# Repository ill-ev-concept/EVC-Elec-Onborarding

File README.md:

@ -1,42 +0,0 @@
# EVC-Elec-Onborarding

Hello onboarding members!

We're going to use this repo as a way for you guys to get practice using Github and EV Concepts workflow. This repo is going to be organized the same way that our main repo (EVC-PCB) is. 

First, let us look at what you need before you start. You need to download at least KiCAD 10 and Git. I also recommened getting Github Desktop

https://www.kicad.org/download/\
https://git-scm.com/install/\
https://desktop.github.com/download/

Also take a look at the documentation for our main repo. We will follow the exact same structure, but change a few variables in order for it to function with this repo. 

https://github.com/ill-ev-concept/EVC-PCB/blob/main/README.md

Let's look at the section where we set paths in KiCAD. We use ```EVC_SYMBOL_DIR```, ```EVC_FOOTPRINT_DIR```, and ```EVC_3DMODEL_DIR``` as variables to set paths for our main repo. In this repo, we will be using different paths. Create three varibles called ```EVCOB_SYMBOL_DIR```, ```EVCOB_FOOTPRINT_DIR```, and ```EVCOB_3DMODEL_DIR```. Link these to the location of the ```symbols```, ```footprints```, and ```3d_models``` folders contained with ```libs-ob``` folder.

It should look like below:

Similarly, we will be needing KiCAD to look at the given library. We can do this by going to "Preferences" and finding either "Manage Symbol Libraries" or "Manage Footprint Libraries". Opening either brings up a window where we can select "Project Specific Libraries" where we can add paths. Click the folder icon and add the wanted library. If you set the path up correctly, the library path will contain  ```${EVCON_SYMBOL_DIR}```, ```${EVCON_FOOTPRINT_DIR}```, or ```${EVCON_3DMODEL_DIR}```. 

It will look like below if done correctly.

Now that your paths are set up properly, its important to use Git and Github properly. Read the Contributing section of EVC-PCB's README file. It goes into detail of how to contribute and properly pull, merge, and create PRs.

Make sure to push and pull from this specific repo, EVC-Elec-Onboarding, not EVC-PCB. EVC-PCB will be the repo you work in after onboarding. Right now, we want to see your work in this repo.

If you have any questions, feel free to message either Miles (mileskubik), Himesh (hotmesh), or Ethan (whybd) on Discord or find us after a meeting. 

Good luck designing!

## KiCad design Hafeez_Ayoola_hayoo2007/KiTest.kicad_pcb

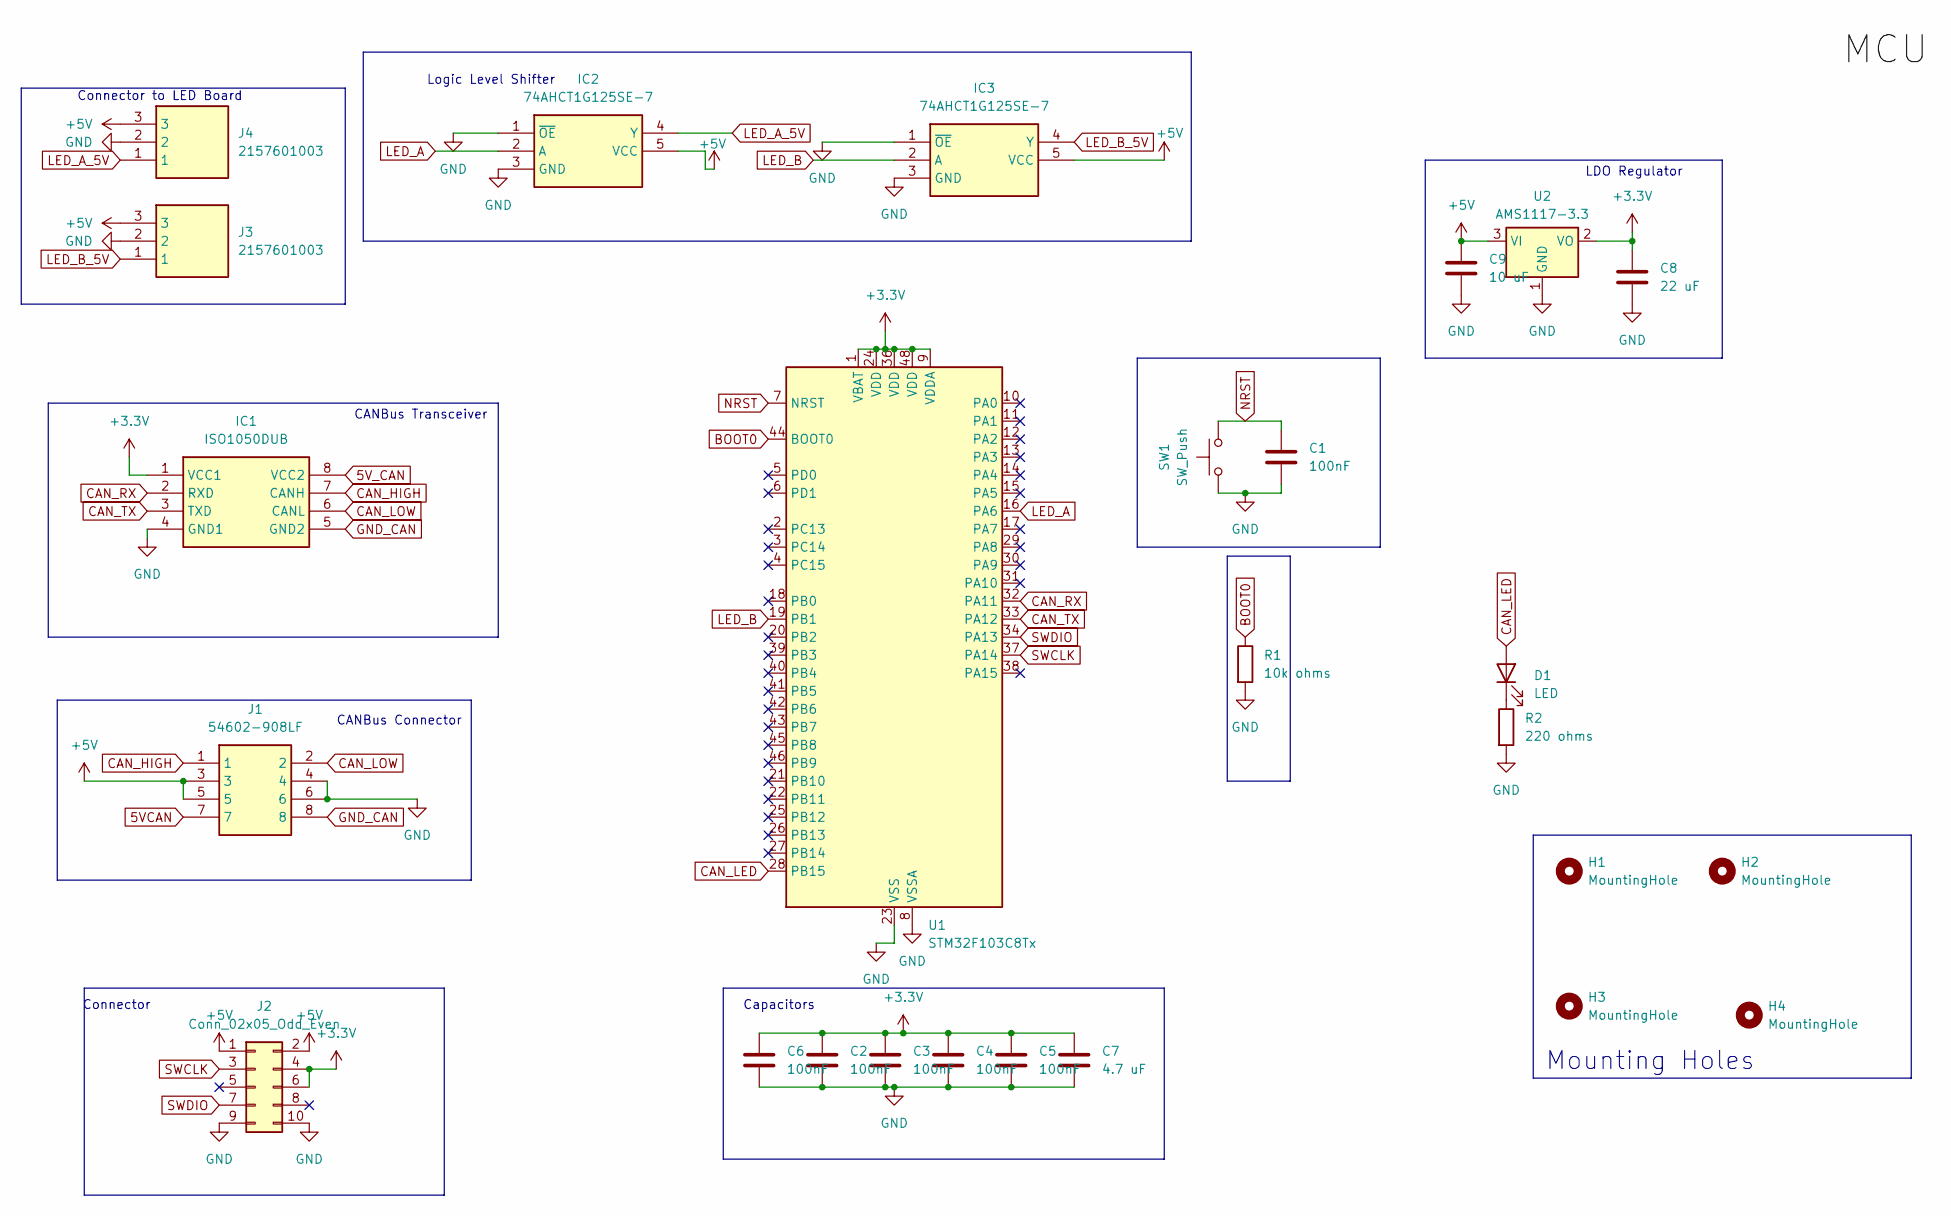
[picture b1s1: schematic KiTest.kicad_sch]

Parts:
C1, C2, C3, C4, C5, C6: 100nF; C_0805_2012Metric
C7: 4.7 uF; C_0805_2012Metric
C8: 22 uF; C_0805_2012Metric
C9: 10 uF; C_0805_2012Metric
D1: LED; D_0805_2012Metric
H1, H2, H3, H4: MountingHole; MountingHole_3.2mm_M3
IC1: ISO1050DUB; SOP-8_6.62x9.15mm_P2.54mm; Manufacturer_Part_Number ISO1050DUB; Mouser Part Number 595-ISO1050DUB
IC2, IC3: 74AHCT1G125SE-7; SOT-353_SC-70-5; Manufacturer_Part_Number 74AHCT1G125SE-7; Mouser Part Number 621-74AHCT1G125SE-7
J1: 54602-908LF; RJ45_Amphenol_54602-x08_Horizontal; Manufacturer_Part_Number 54602-908LF
J2: Conn_02x05_Odd_Even; PinHeader_2x05_P2.54mm_Vertical
J3, J4: 2157601003; Molex_Micro-Fit_3.0_43650-0300_1x03_P3.00mm_Horizontal; Manufacturer_Part_Number 2157601003
R1: 10k ohms; R_0805_2012Metric
R2: 220 ohms; R_0805_2012Metric
SW1: SW_Push; SW_SPST_EVQQ2
U1: STM32F103C8Tx; LQFP-48_7x7mm_P0.5mm
U2: AMS1117-3.3; SOT-223-3_TabPin2

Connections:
5VCAN: J1.7
5V_CAN: IC1.8 (VCC2)
+3.3V: C2.1, C3.1, C4.1, C5.1, C6.1, C7.1, C8.1, IC1.1 (VCC1), J2.4, J2.6, U1.1 (VBAT), U1.9 (VDDA), U1.24 (VDD), U1.36 (VDD), U1.48 (VDD), U2.2 (VO)
+5V: C9.1, IC2.5 (VCC), IC3.5 (VCC), J1.3, J1.5, J2.1, J2.2, J3.3, J4.3, U2.3 (VI)
BOOT0: R1.1, U1.44 (BOOT0)
CAN_HIGH: IC1.7 (CANH), J1.1
CAN_LED: D1.2 (A), U1.28 (PB15)
CAN_LOW: IC1.6 (CANL), J1.2
CAN_RX: IC1.2 (RXD), U1.32 (PA11)
CAN_TX: IC1.3 (TXD), U1.33 (PA12)
GND: C1.2, C2.2, C3.2, C4.2, C5.2, C6.2, C7.2, C8.2, C9.2, IC1.4 (GND1), IC2.1 (~OE), IC2.3 (GND), IC3.1 (~OE), IC3.3 (GND), J1.4, J1.6, J2.9, J2.10, J3.2, J4.2, R1.2, R2.2, SW1.1, U1.8 (VSSA), U1.23 (VSS), U1.35 (VSS), U1.47 (VSS), U2.1 (GND)
GND_CAN: IC1.5 (GND2), J1.8
LED_A: IC2.2 (A), U1.16 (PA6)
LED_A_5V: IC2.4 (Y), J4.1
LED_B: IC3.2 (A), U1.19 (PB1)
LED_B_5V: IC3.4 (Y), J3.1
NRST: C1.1, SW1.2, U1.7 (NRST)
unnamed: D1.1 (K), R2.1
SWCLK: J2.3, U1.37 (PA14)
SWDIO: J2.7, U1.34 (PA13)

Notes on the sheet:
Mounting Holes
LDO Regulator
CANBus Transceiver
Capacitors
Logic Level Shifter
Connector
CANBus Connector
Connector to LED Board

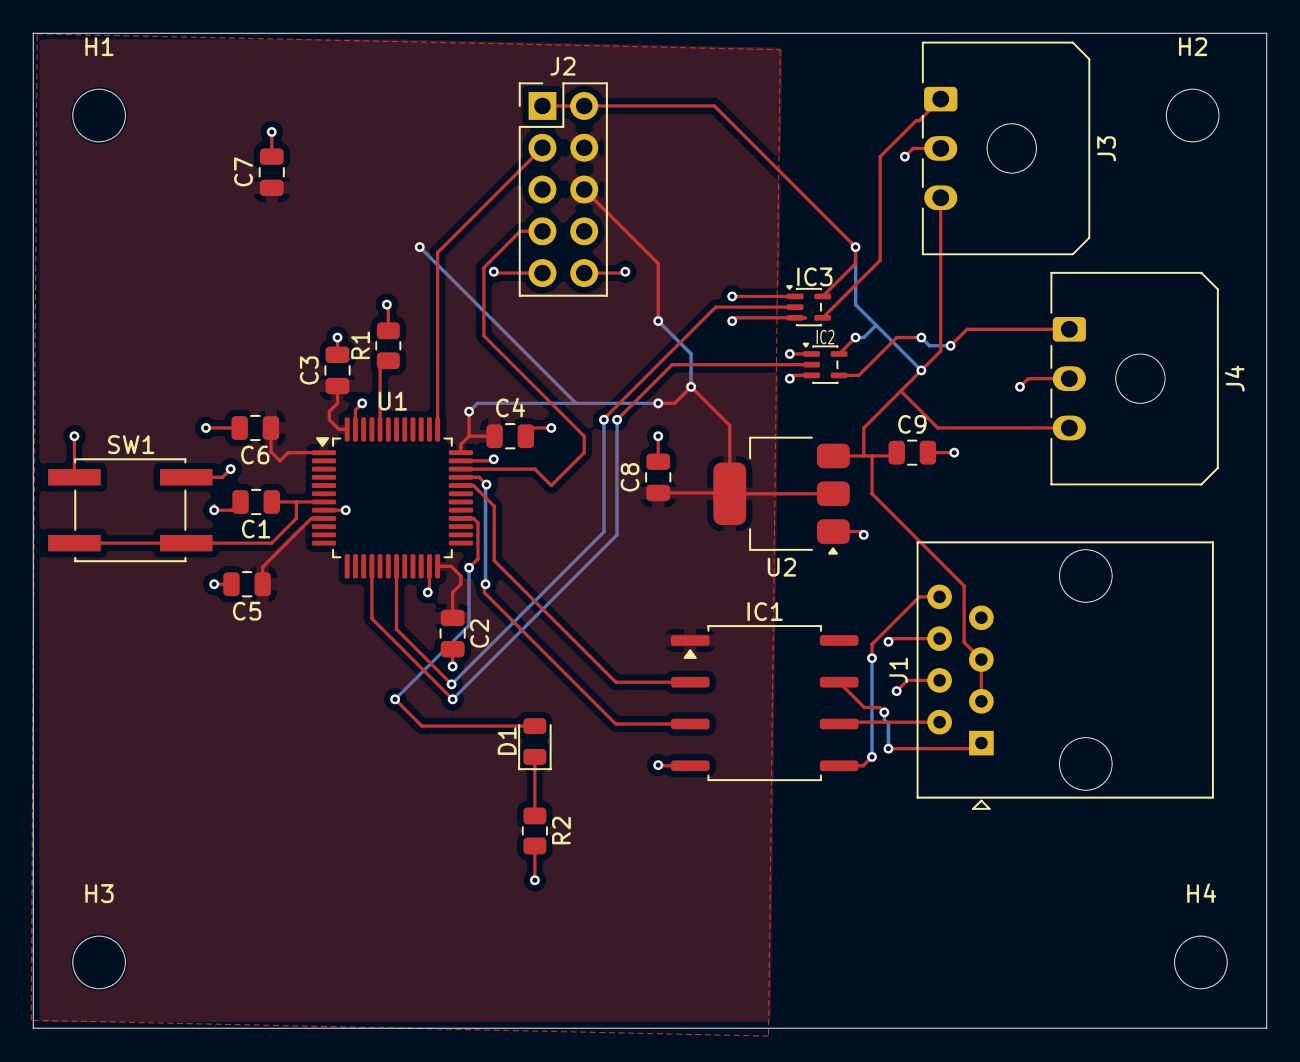
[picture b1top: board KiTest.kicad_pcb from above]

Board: 2 copper layers, 75.0 x 60.5 mm, 26 parts (0 on the bottom side), 18 nets.

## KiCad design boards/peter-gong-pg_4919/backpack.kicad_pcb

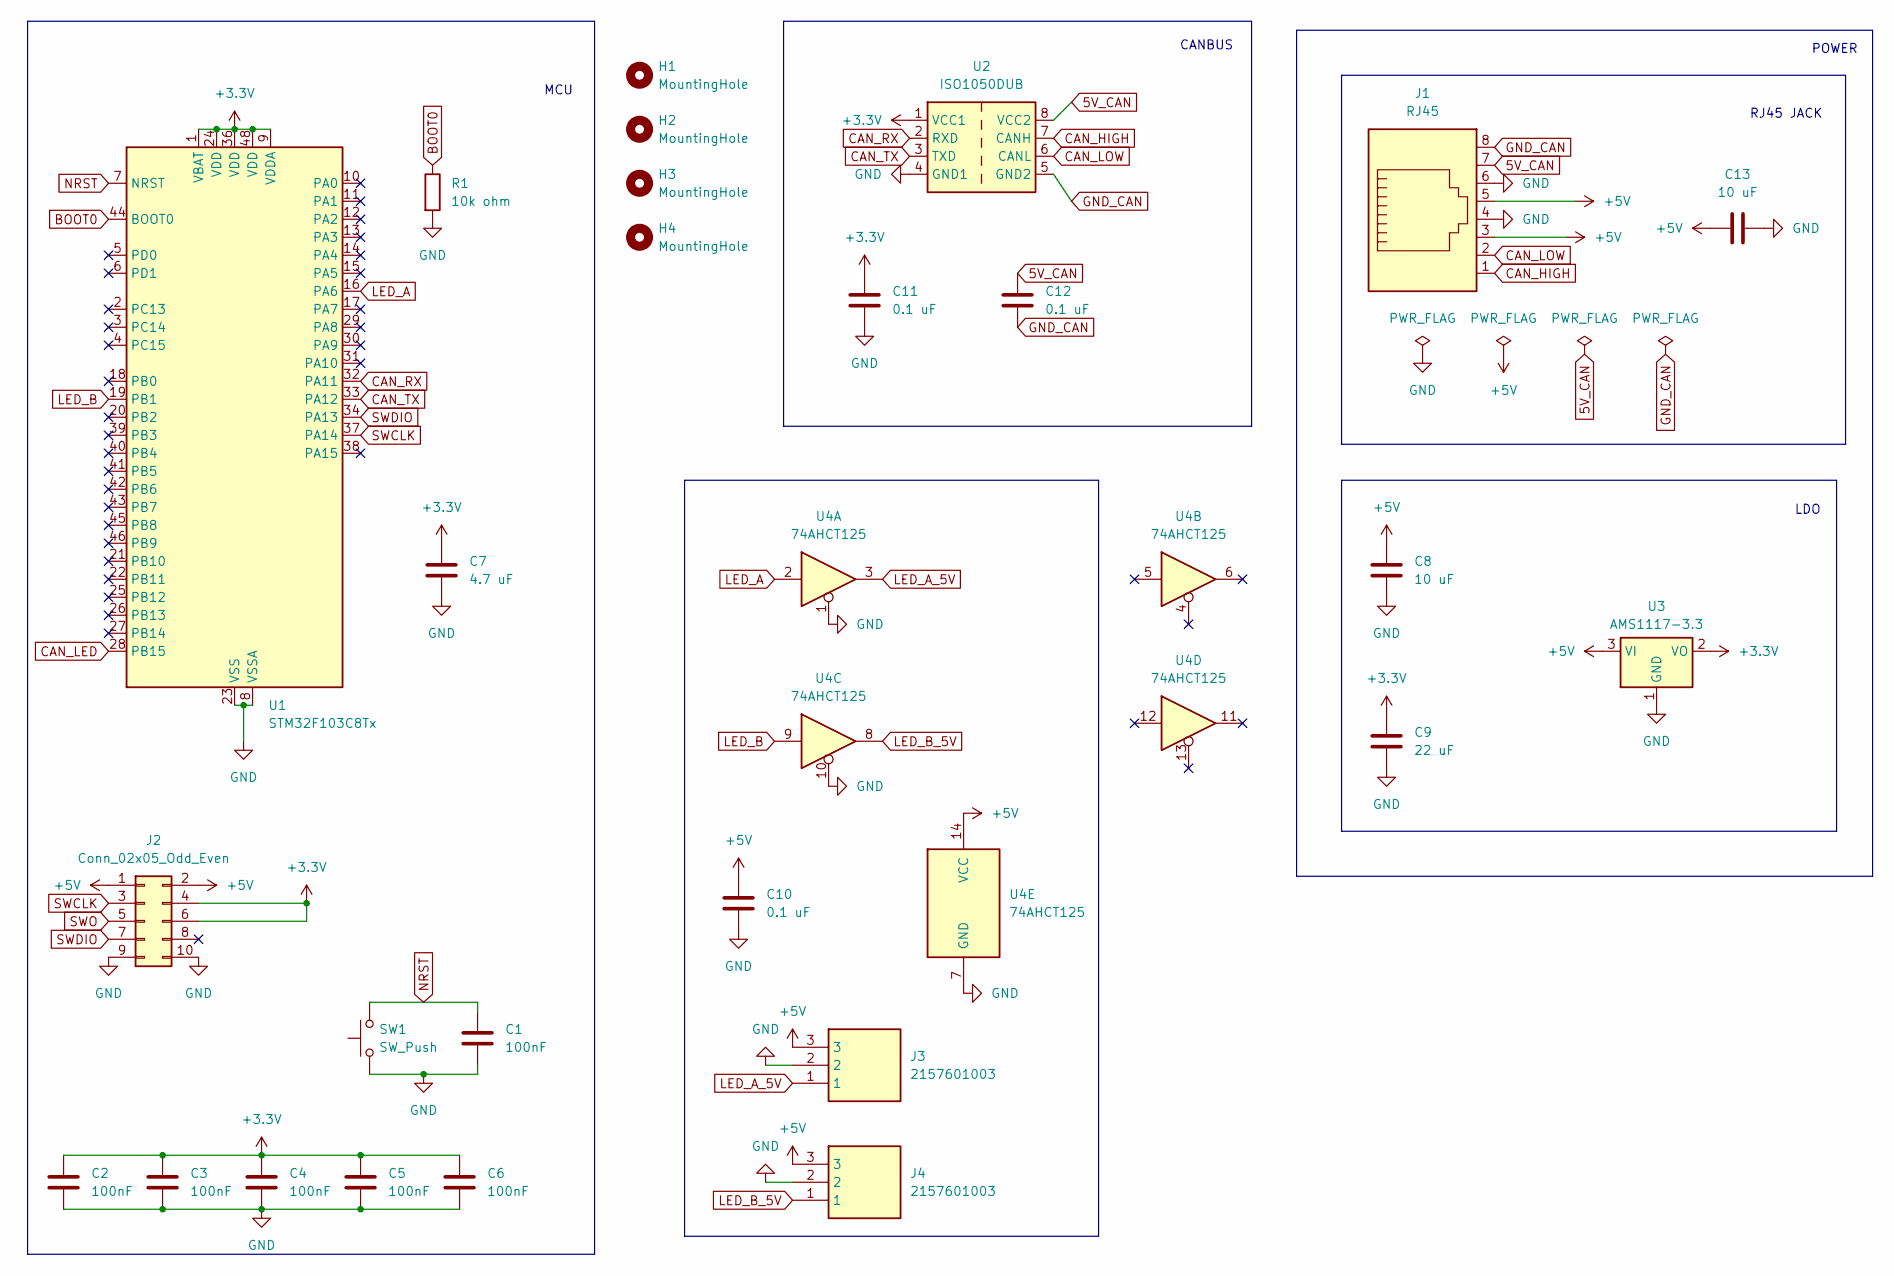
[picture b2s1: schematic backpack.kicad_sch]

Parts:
C1, C2, C3, C4, C5, C6: 100nF; C_0603_1608Metric
C7: 4.7 uF; C_0603_1608Metric
C8, C13: 10 uF; C_0603_1608Metric
C9: 22 uF; C_0603_1608Metric
C10, C11, C12: 0.1 uF; C_0603_1608Metric
H1, H2, H3, H4: MountingHole; MountingHole_3.2mm_M3
J1: RJ45; RJ45_Amphenol_54602-x08_Horizontal
J2: Conn_02x05_Odd_Even; PinHeader_2x05_P2.54mm_Vertical
J3, J4: 2157601003; 215760YY03; Manufacturer_Part_Number 2157601003
R1: 10k ohm; R_0603_1608Metric
SW1: SW_Push; SW_SPST_EVQQ2
U1: STM32F103C8Tx; LQFP-48_7x7mm_P0.5mm
U2: ISO1050DUB; SOP-8_6.62x9.15mm_P2.54mm
U3: AMS1117-3.3; SOT-223-3_TabPin2
U4: 74AHCT125; TSSOP-14_4.4x5mm_P0.65mm

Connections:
5V_CAN: C12.1, J1.7, U2.8 (VCC2)
+3.3V: C2.1, C3.1, C4.1, C5.1, C6.1, C7.1, C9.1, C11.1, J2.4, J2.6, U1.1 (VBAT), U1.9 (VDDA), U1.24 (VDD), U1.36 (VDD), U1.48 (VDD), U2.1 (VCC1), U3.2 (VO)
+5V: C8.1, C10.1, C13.1, J1.3, J1.5, J2.1, J2.2, J3.3, J4.3, U3.3 (VI), U4.14 (VCC)
BOOT0: R1.1, U1.44 (BOOT0)
CAN_HIGH: J1.1, U2.7 (CANH)
CAN_LED: U1.28 (PB15)
CAN_LOW: J1.2, U2.6 (CANL)
CAN_RX: U1.32 (PA11), U2.2 (RXD)
CAN_TX: U1.33 (PA12), U2.3 (TXD)
GND: C1.2, C2.2, C3.2, C4.2, C5.2, C6.2, C7.2, C8.2, C9.2, C10.2, C11.2, C13.2, J1.4, J1.6, J2.9, J2.10, J3.2, J4.2, R1.2, SW1.1, U1.8 (VSSA), U1.23 (VSS), U1.35 (VSS), U1.47 (VSS), U2.4 (GND1), U3.1 (GND), U4.1, U4.7 (GND), U4.10
GND_CAN: C12.2, J1.8, U2.5 (GND2)
LED_A: U1.16 (PA6), U4.2
LED_A_5V: J3.1, U4.3
LED_B: U1.19 (PB1), U4.9
LED_B_5V: J4.1, U4.8
NRST: C1.1, SW1.2, U1.7 (NRST)
SWCLK: J2.3, U1.37 (PA14)
SWDIO: J2.7, U1.34 (PA13)
SWO: J2.5

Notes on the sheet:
MCU
POWER
LDO
CANBUS
RJ45 JACK

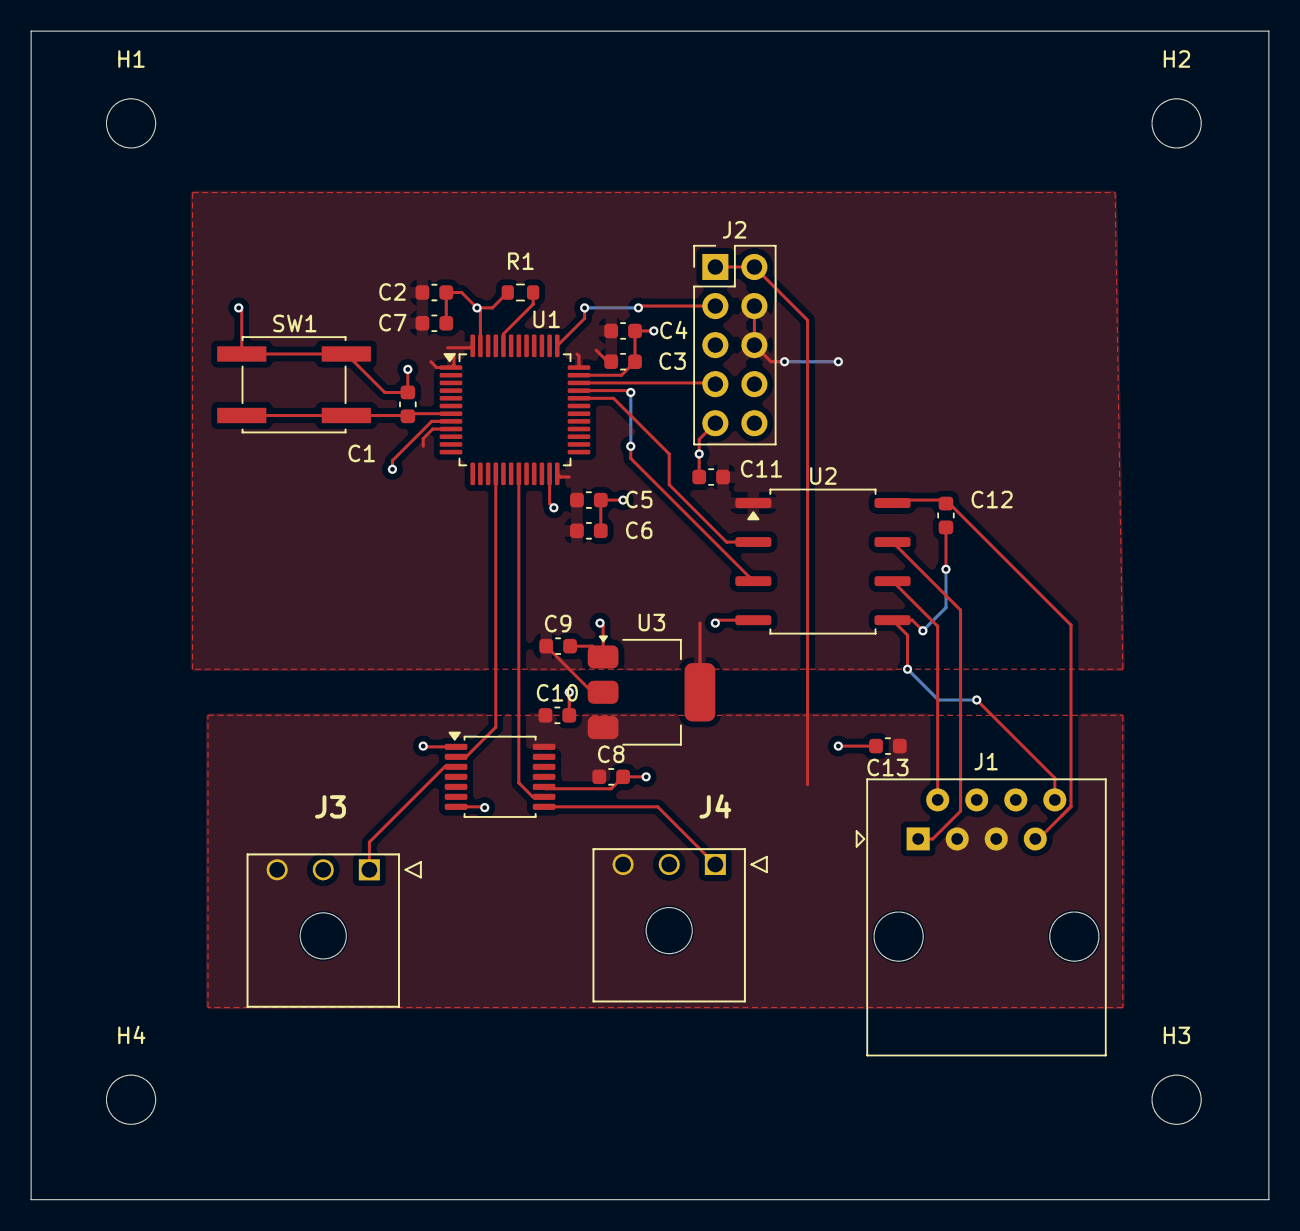
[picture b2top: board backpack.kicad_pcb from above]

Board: 2 copper layers, 80.5 x 76.0 mm, 27 parts (0 on the bottom side), 17 nets.

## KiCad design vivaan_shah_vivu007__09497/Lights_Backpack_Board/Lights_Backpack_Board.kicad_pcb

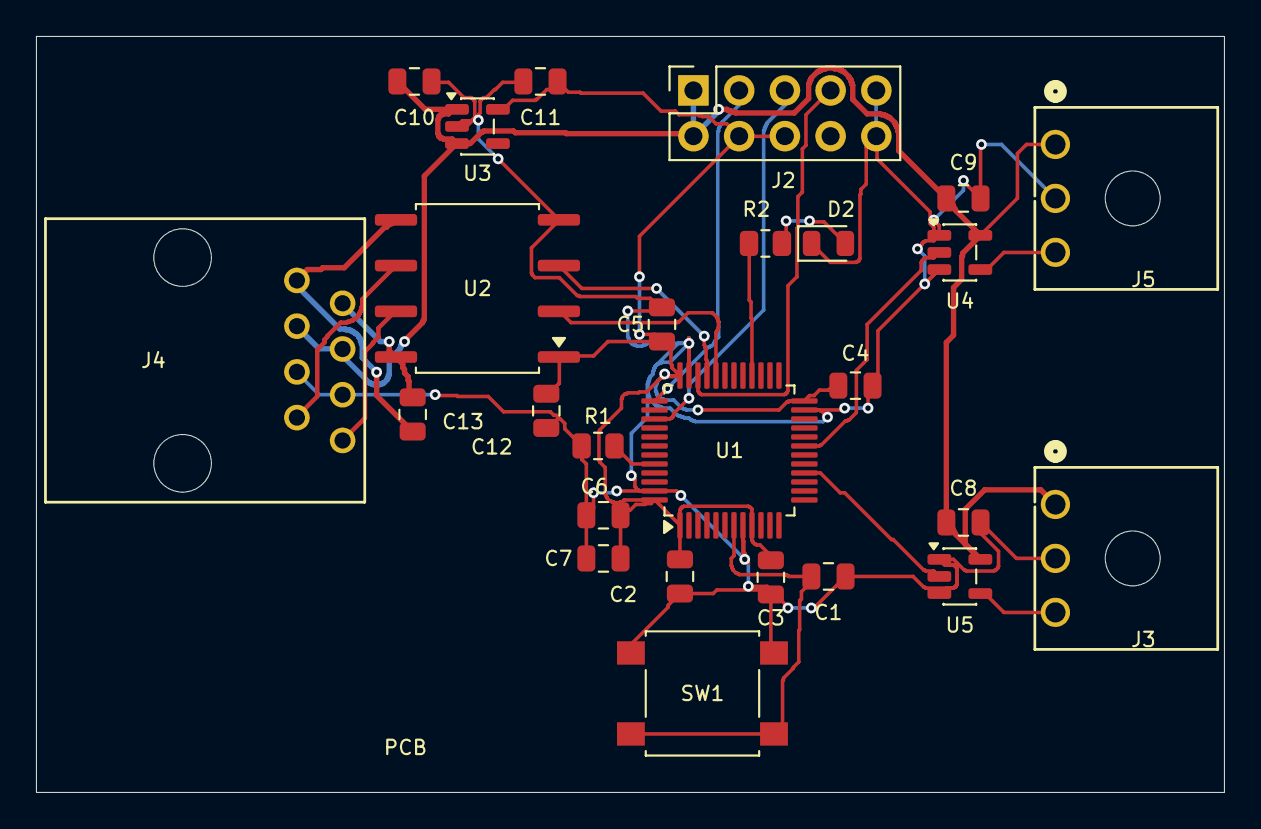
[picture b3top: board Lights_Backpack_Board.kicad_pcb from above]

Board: 2 copper layers, 66.0 x 42.0 mm, 26 parts (0 on the bottom side), 20 nets.

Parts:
C1, C2, C3, C4, C5, C6, C12, C13: 100nF; C_0805_2012Metric
C7: 4.7 uF; C_0805_2012Metric
C8, C9: 0.1 uF; C_0805_2012Metric
C10, C11: 1 uF; C_0805_2012Metric
D2: LED; LED_0805_2012Metric
J2: Conn_02x05_Odd_Even; PinSocket_2x05_P2.54mm_Vertical
J3, J5: Conn_01x03; CONN_2157600003-SD_03_PEG_MOL
J4: 54602-908LF
R1: 10k ohm; R_0805_2012Metric
R2: 220 ohm; R_0805_2012Metric
SW1: SW_Push; SW_SPST_B3S-1000
U1: STM32F103C8Tx; LQFP-48_7x7mm_P0.5mm
U2: ISO1050DUB; SOP-8_6.62x9.15mm_P2.54mm
U3: AP2112K-3.3; SOT-23-5
U4, U5: 74AHCT1G125; SOT-23-5

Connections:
5V_CAN: C13.1, J4.7, U2.8 (VCC2)
+3.3V: C2.1, C3.1, C4.1, C5.1, C6.1, C7.1, C11.1, C12.1, J2.4, J2.6, U1.1 (VBAT), U1.9 (VDDA), U1.24 (VDD), U1.36 (VDD), U1.48 (VDD), U2.1 (VCC1), U3.5 (VOUT)
+5V: C8.1, C9.1, C10.1, J2.1, J2.2, J3.1, J4.5, J4.6, J5.1, U3.1 (VIN), U3.3 (EN), U4.5 (VCC), U5.5 (VCC)
BOOT0: R1.1, U1.44 (BOOT0)
CAN_HIGH: J4.1, U2.7 (CANH)
CAN_LED: R2.2, U1.28 (PB15)
CAN_LOW: J4.2, U2.6 (CANL)
CAN_RX: U1.32 (PA11), U2.2 (RXD)
CAN_TX: U1.33 (PA12), U2.3 (TXD)
GND: C1.2, C2.2, C3.2, C4.2, C5.2, C6.2, C7.2, C8.2, C9.2, C10.2, C11.2, C12.2, D2.1 (K), J2.9, J2.10, J3.2, J4.3, J4.4, J5.2, R1.2, SW1.1, U1.8 (VSSA), U1.23 (VSS), U1.35 (VSS), U1.47 (VSS), U2.4 (GND1), U3.2 (GND), U4.1, U4.3 (GND), U5.1, U5.3 (GND)
GND_CAN: C13.2, J4.8, U2.5 (GND2)
LED_A_5V: J3.3, U5.4
LED_B_5V: J5.3, U4.4
NRST: C1.1, SW1.2, U1.7 (NRST)
unnamed: D2.2 (A), R2.1
SWCLK: J2.3, U1.37 (PA14)
SWDIO: J2.7, U1.34 (PA13)
SWO: J2.5, U1.39 (PB3)
TIM3_CH1: U1.16 (PA6), U5.2
TIM3_CH4: U1.19 (PB1), U4.2

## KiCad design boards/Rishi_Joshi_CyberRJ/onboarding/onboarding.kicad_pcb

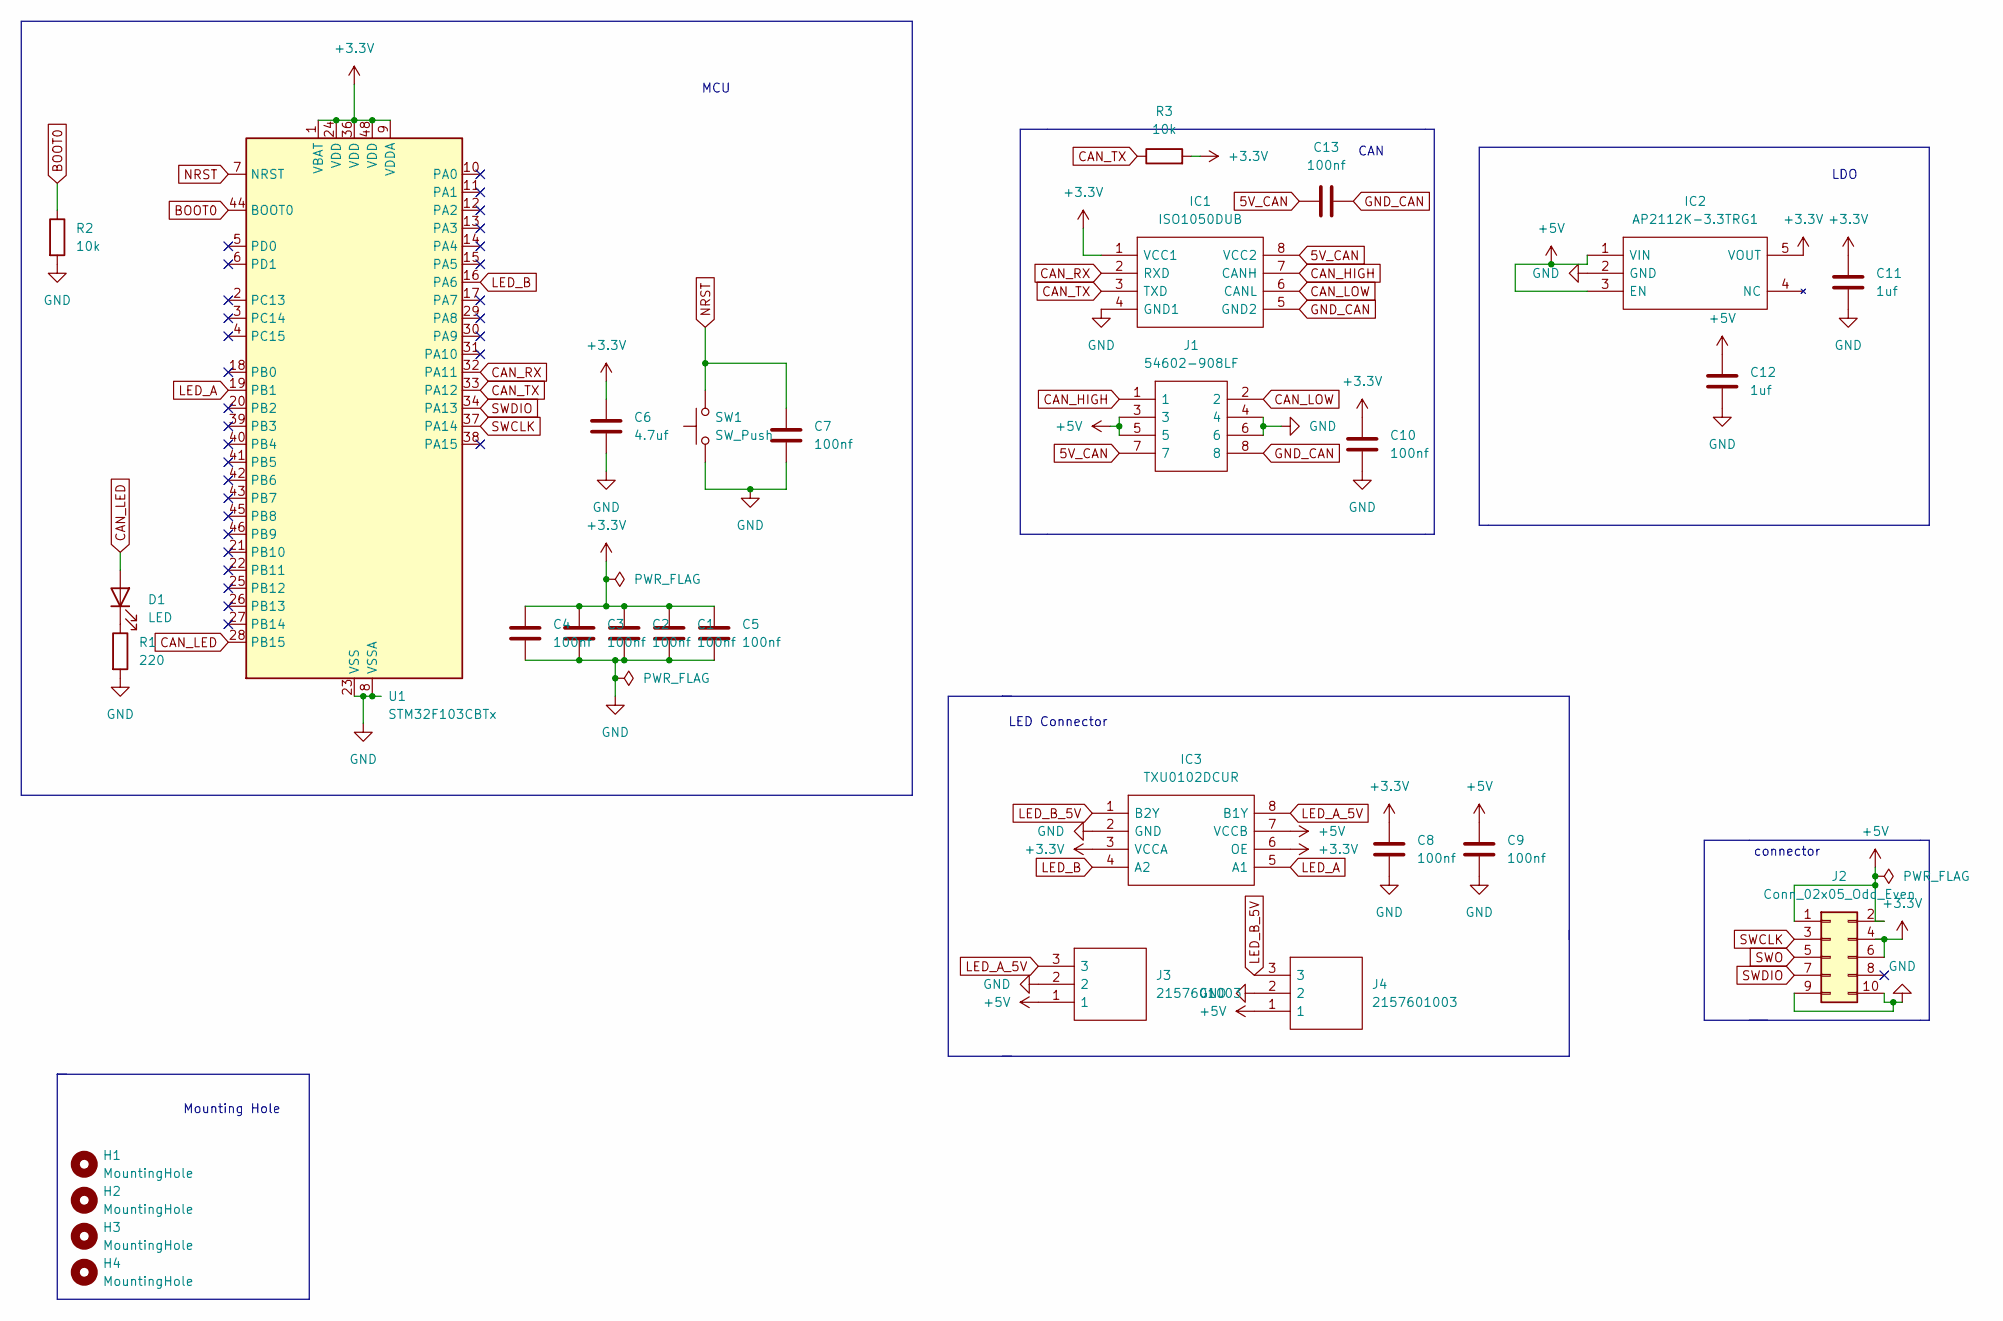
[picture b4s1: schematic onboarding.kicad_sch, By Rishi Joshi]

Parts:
C1, C2, C3, C4, C5, C7, C8, C9, C10, C13: 100nf; C_0805_2012Metric
C6: 4.7uf; C_0805_2012Metric
C11, C12: 1uf; C_0805_2012Metric
D1: LED; LED_0805_2012Metric
H1, H2, H3, H4: MountingHole; MountingHole_3.2mm_M3
IC1: ISO1050DUB; SOP254P1040X485-8N; Manufacturer_Part_Number ISO1050DUB; Mouser Part Number 595-ISO1050DUB
IC2: AP2112K-3.3TRG1; SOT95P285X140-5N; Manufacturer_Part_Number AP2112K-3.3TRG1; Mouser Part Number 621-AP2112K-3.3TRG1
IC3: TXU0102DCUR; SOP50P310X90-8N; Manufacturer_Part_Number TXU0102DCUR; Mouser Part Number 595-TXU0102DCUR
J1: 54602-908LF; 54602908LF; Manufacturer_Part_Number 54602-908LF
J2: Conn_02x05_Odd_Even; PinHeader_2x05_P2.54mm_Vertical
J3, J4: 2157601003; 215760YY03; Manufacturer_Part_Number 2157601003
R1: 220; R_0805_2012Metric
R2, R3: 10k; R_0805_2012Metric
SW1: SW_Push; SW_SPST_EVQQ2
U1: STM32F103CBTx; LQFP-48_7x7mm_P0.5mm

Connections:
5V_CAN: C13.1, IC1.8 (VCC2), J1.7
+3.3V: C1.1, C2.1, C3.1, C4.1, C5.1, C6.1, C8.1, C10.1, C11.1, IC1.1 (VCC1), IC2.5 (VOUT), IC3.3 (VCCA), IC3.6 (OE), J2.4, J2.6, R3.2, U1.1 (VBAT), U1.9 (VDDA), U1.24 (VDD), U1.36 (VDD), U1.48 (VDD)
+5V: C9.1, C12.1, IC2.1 (VIN), IC2.3 (EN), IC3.7 (VCCB), J1.3, J1.5, J2.1, J2.2, J3.1, J4.1
BOOT0: R2.1, U1.44 (BOOT0)
CAN_HIGH: IC1.7 (CANH), J1.1
CAN_LED: D1.2 (A), U1.28 (PB15)
CAN_LOW: IC1.6 (CANL), J1.2
CAN_RX: IC1.2 (RXD), U1.32 (PA11)
CAN_TX: IC1.3 (TXD), R3.1, U1.33 (PA12)
GND: C1.2, C2.2, C3.2, C4.2, C5.2, C6.2, C7.2, C8.2, C9.2, C10.2, C11.2, C12.2, IC1.4 (GND1), IC2.2 (GND), IC3.2 (GND), J1.4, J1.6, J2.9, J2.10, J3.2, J4.2, R1.2, R2.2, SW1.1, U1.8 (VSSA), U1.23 (VSS), U1.35 (VSS), U1.47 (VSS)
GND_CAN: C13.2, IC1.5 (GND2), J1.8
LED_A: IC3.5 (A1), U1.19 (PB1)
LED_A_5V: IC3.8 (B1Y), J3.3
LED_B: IC3.4 (A2), U1.16 (PA6)
LED_B_5V: IC3.1 (B2Y), J4.3
NRST: C7.1, SW1.2, U1.7 (NRST)
unnamed: D1.1 (K), R1.1
SWCLK: J2.3, U1.37 (PA14)
SWDIO: J2.7, U1.34 (PA13)
SWO: J2.5

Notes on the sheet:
MCU
Mounting Hole
connector
LED Connector
LDO
CAN

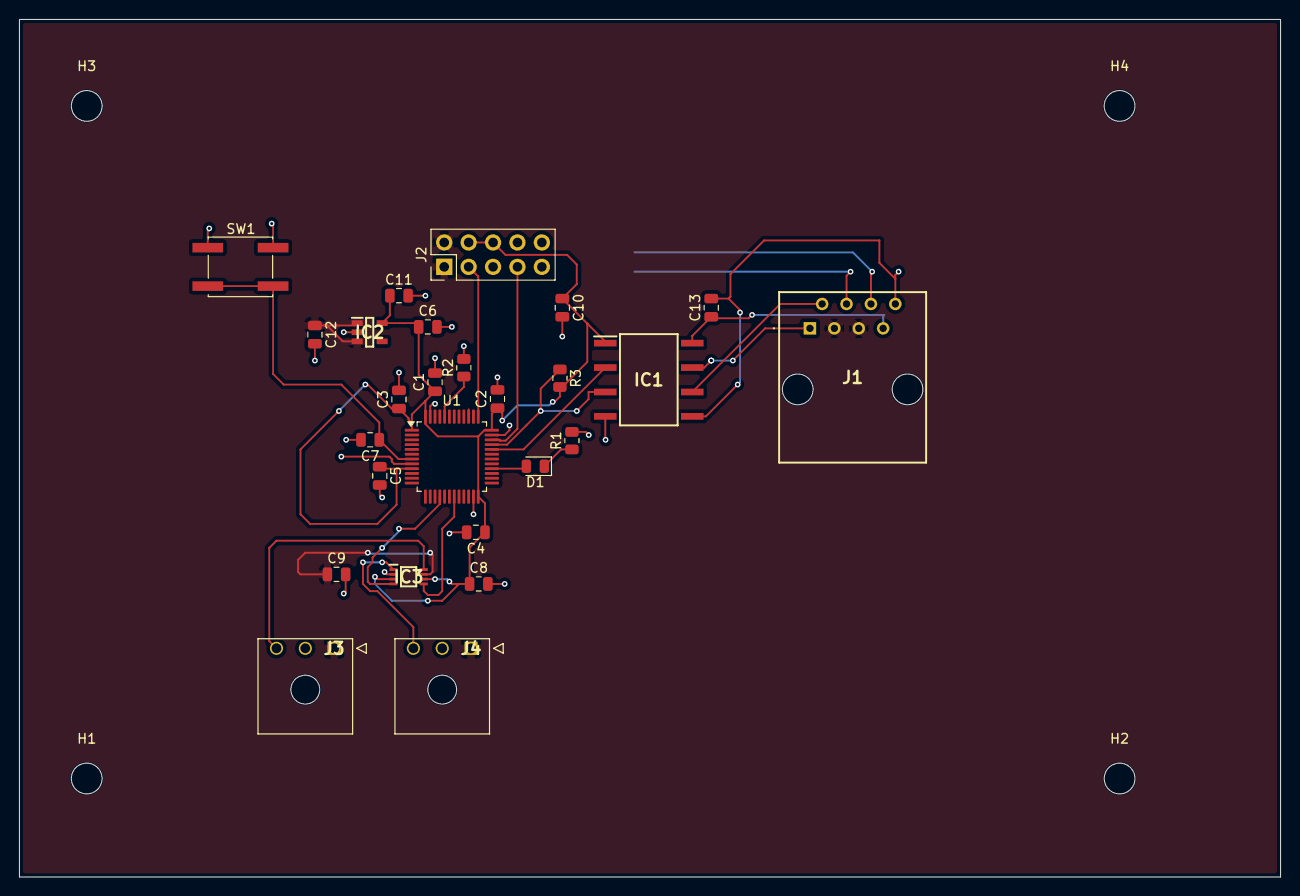
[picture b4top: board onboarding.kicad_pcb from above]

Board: 2 copper layers, 131.2 x 89.2 mm, 30 parts (0 on the bottom side), 19 nets.

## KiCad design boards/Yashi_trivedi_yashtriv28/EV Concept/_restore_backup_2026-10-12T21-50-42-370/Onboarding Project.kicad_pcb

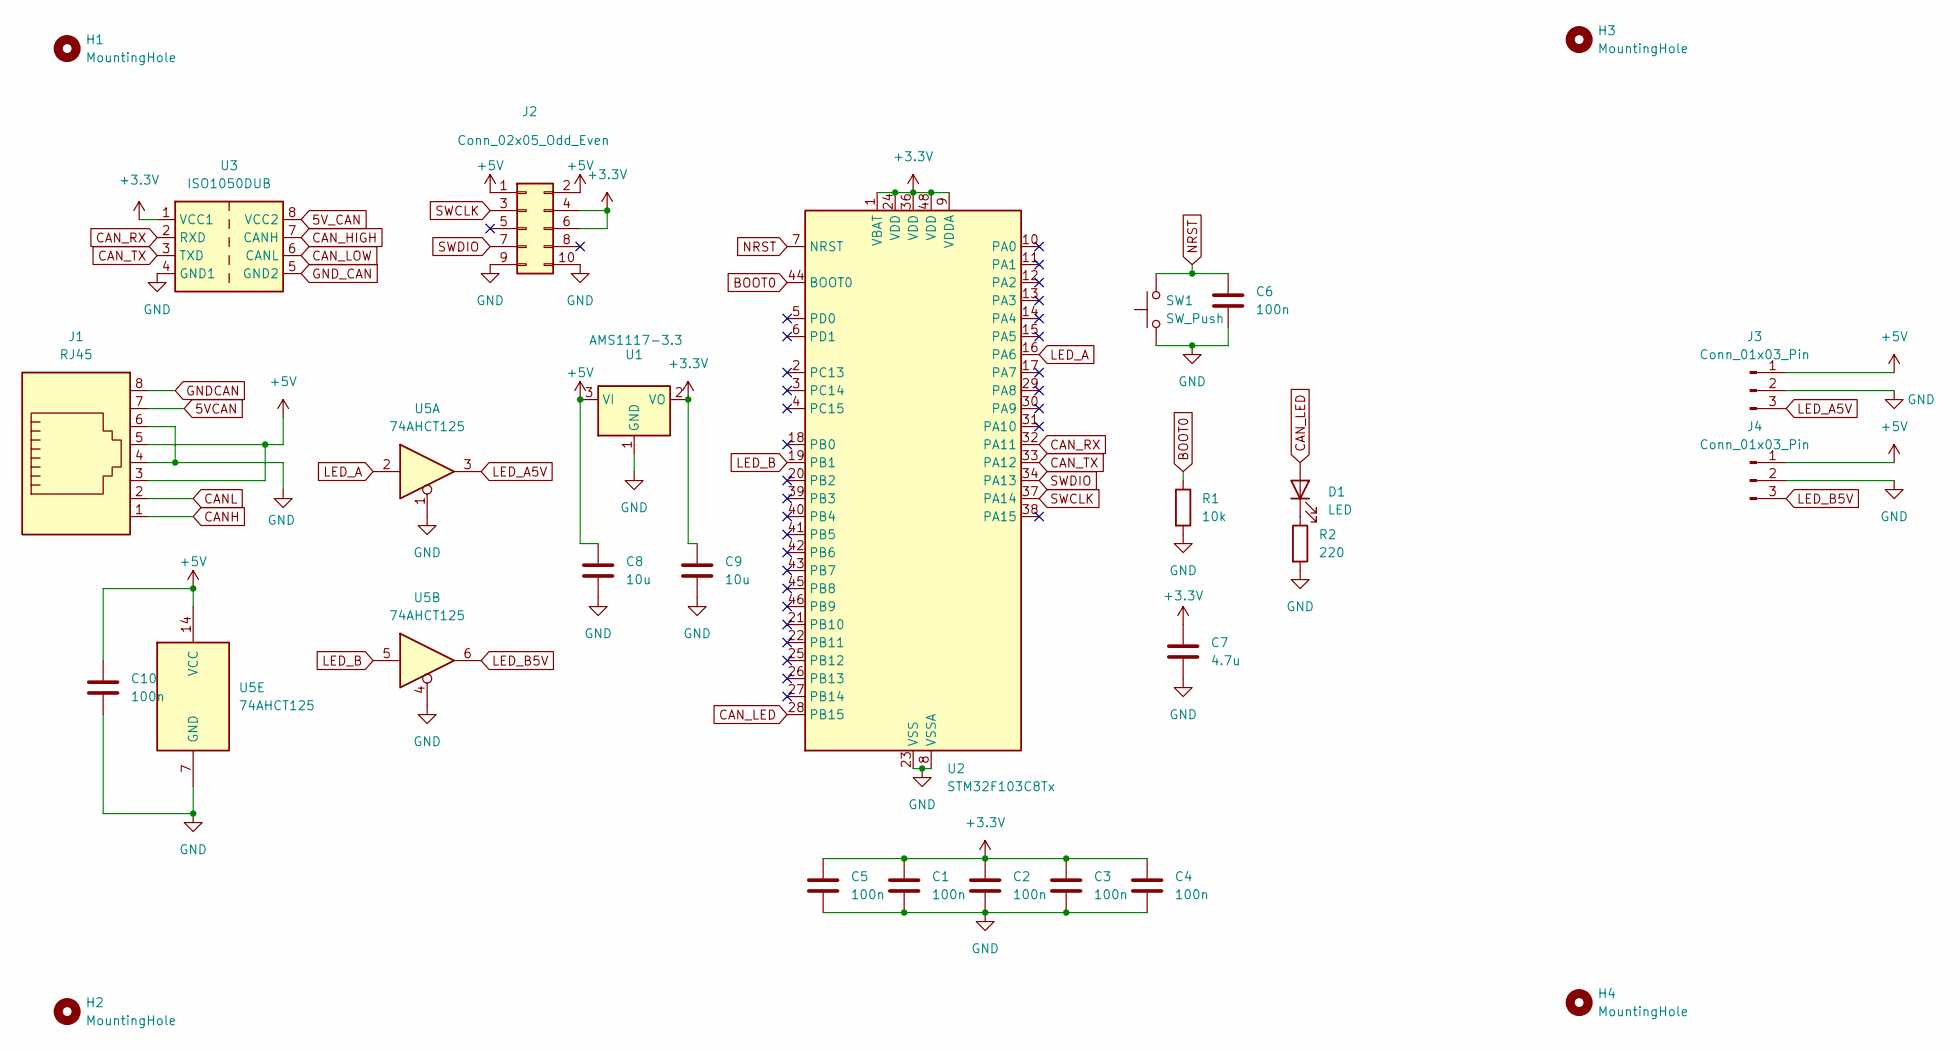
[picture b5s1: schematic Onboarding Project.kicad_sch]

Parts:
C1, C2, C3, C4, C5, C6, C10: 100n; C_0805_2012Metric
C7: 4.7u; C_0805_2012Metric
C8, C9: 10u; C_0805_2012Metric
D1: LED; LED_0805_2012Metric
H1, H2, H3, H4: MountingHole; MountingHole_4.3mm_M4
J1: RJ45; CONN8_2-908LF_AMP
J2: Conn_02x05_Odd_Even; SOP-8_6.62x9.15mm_P2.54mm
J3, J4: Conn_01x03_Pin; CONN_2157600003-SD_03_PEG_MOL
R1: 10k; R_0805_2012Metric
R2: 220; R_0805_2012Metric
SW1: SW_Push; SW_SPST_EVQQ2
U1: AMS1117-3.3; SOT-223-3_TabPin2
U2: STM32F103C8Tx; LQFP48_STM
U3: ISO1050DUB; DUB0008A_N
U5: 74AHCT125; N14

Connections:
5VCAN: J1.7
5V_CAN: U3.8 (VCC2)
+3.3V: C1.1, C2.1, C3.1, C4.1, C5.1, C7.1, C9.1, J2.4, J2.6, U1.2 (VO), U2.1 (VBAT), U2.9 (VDDA), U2.24 (VDD), U2.36 (VDD), U2.48 (VDD), U3.1 (VCC1)
+5V: C8.1, C10.1, J1.3, J1.5, J2.1, J2.2, J3.1, J4.1, U1.3 (VI), U5.14 (VCC)
BOOT0: R1.1, U2.44 (BOOT0)
CANH: J1.1
CANL: J1.2
CAN_HIGH: U3.7 (CANH)
CAN_LED: D1.2 (A), U2.28 (PB15)
CAN_LOW: U3.6 (CANL)
CAN_RX: U2.32 (PA11), U3.2 (RXD)
CAN_TX: U2.33 (PA12), U3.3 (TXD)
GND: C1.2, C2.2, C3.2, C4.2, C5.2, C6.2, C7.2, C8.2, C9.2, C10.2, J1.4, J1.6, J2.9, J2.10, J3.2, J4.2, R1.2, R2.2, SW1.1, U1.1 (GND), U2.8 (VSSA), U2.23 (VSS), U2.35 (VSS), U2.47 (VSS), U3.4 (GND1), U5.1, U5.4, U5.7 (GND)
GNDCAN: J1.8
GND_CAN: U3.5 (GND2)
LED_A: U2.16 (PA6), U5.2
LED_A5V: J3.3, U5.3
LED_B: U2.19 (PB1), U5.5
LED_B5V: J4.3, U5.6
NRST: C6.1, SW1.2, U2.7 (NRST)
unnamed: D1.1 (K), R2.1
SWCLK: J2.3, U2.37 (PA14)
SWDIO: J2.7, U2.34 (PA13)
SWO: J2.5

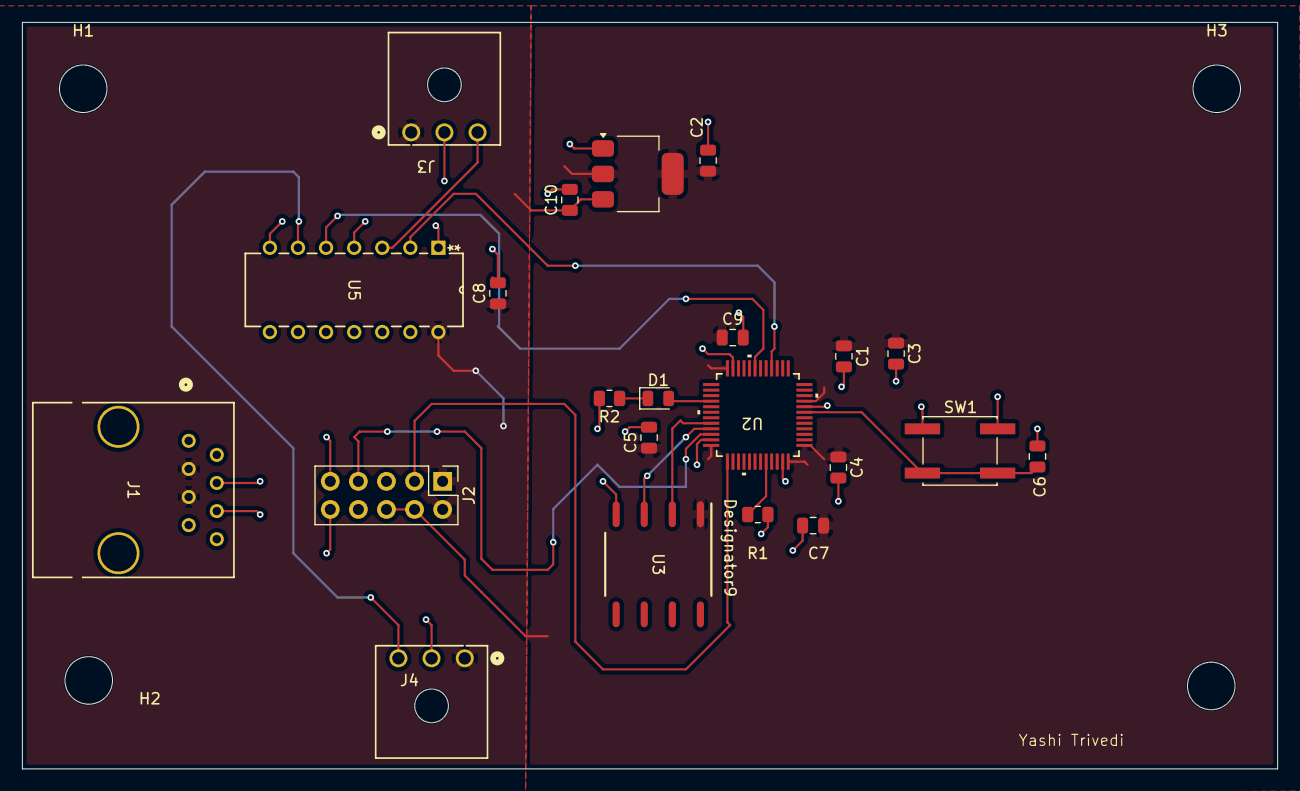
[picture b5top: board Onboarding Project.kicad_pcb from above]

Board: 2 copper layers, 113.5 x 67.5 mm, 26 parts (0 on the bottom side), 15 nets.
